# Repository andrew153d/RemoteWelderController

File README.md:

# RemoteWelderController #

A pair of devices meant to retrofit older welders with wireless connectivity. This document covers the usage and mechanical makeup, the cost overview can be found [here](https://github.com/andrew153d/RemoteWelderController/tree/main/hardware). There is also a preview of the site at this [link](https://andrew153d.github.io/RemoteWelderController/firmware/webpage/web_controller.html), note functionality is limited.

--- 

## Usage

There are three main modes of operation: Standard, Web Control, and Extended Web Control

### Standard Control

To enter standard control mode, toggle the Transmitter power switch to the 'ON' position and press the Power button on the Receiver. While the devices are searching for each other, their status LEDs will flash blue and will transition to solid green when connected. Rotation input on the control knob will result in proportional motion on the output shaft of the receiver. 

### Web Control

Web Control Mode will allow the user to make use of the web interface to control the output of the receiver. Press the power button on the receiver to turn the device on. After the status LED flashes blue, hold the power button for 3 seconds or until the LED turns to solid green. Connect your phone to the wifi network named Weld_---, open a browser and go to 'Weld.local'.

### Extended Web Control

Extended Web Control uses the Transmitter to host the webpage and repeats control to the receiver. After turning on both devices, hold both the up and down buttons for 3 seconds until the status LED turns green. Connect your phone to the Wifi network named Weld_--- and open the site 'Weld.Local'. In order to increase the usable distance, place the transmitter between the user and the receiver.

## Mechanical Details

### Web Interface 
<div align="center">
<p>
The webpage for control and configuration. Of course you can stay loyal to your brand while still bringing your welder into the modern world. The dial can be dragged to rotate, or the user can swipe the arrows at the bottom to rotate the knob. The lock button will match rotation on the output to the knob on the webpage. The align button will automatically measure the range of the output and scale the input accordingly. Settings and more configuration options can be accessed via the menu on the top left. 
</p>

</div>

### Transmitter

<div align="center">
<p>
Top view of the pelican case with reciever stowed on the right side.
</p>

</div>

<div align="center">

<p style="margin:0px 100px;">
The charge port cap can be removed to expose the USBC port and charge the device.
</p>

</div>

<div align="center">
<p style="margin:0px 100px;">
The circuit board and battery pack get mounted under the faceplate. Not shown is a cover to shield the electronics from debris under the faceplate.
</p>

</div>

### Receiver

<div align="center">
    <p>
        Receiver is shown without belt mechanism. The hatch is biased closed by a torsion spring and sealed against the surface with a O-ring.
    </p>

</div>
<div align="center">
    <p>
    Shown below is the hatch on the receiver that exposes the charging port, status led, and power button. The power button serves multiple alternative functions described in the usage section.
    </p>
    
</div>
<div align="center">
    <p>
    There are several seals on the receiver that maintain water resistance. The upper seal gets compressed between the upper cover and the case. There is also a seal on the access hatch as well as around the motor shaft.
    </p>

</div>

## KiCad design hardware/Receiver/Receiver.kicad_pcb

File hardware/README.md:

# BOM Overview and Cost #
This table is based on building 5 receivers and 5 transmitters. The total cost to build comes to $1050 and the individual cost to build of $210. Assuming four are sold at $300, the venture would profit $150.
## Transmitter ##

### Hardware Components ###

| Item                | QT per device | Total QT | Cost per device | Total Cost | Purchase QT | Purchase Cost |
|---------------------|---------------|----------|-----------------|------------|-------------|---------------|
| [Pelican Case](https://www.pelican.com/us/en/product/cases/protector/1120?sku=1120-000-110) | 1 | 5 | $45.00 | $225 | 5 | $225 |
| [Momentary Switches](https://a.co/d/eoz4Ket) | 2 | 10 | $1.5 | $15.00 | 12 | $18.00 |
| [Power Switch](https://a.co/d/50zdfZq) | 1 | 5 | $0.89 | $4.5 | 10 | $9.00 |
| Aluminum Face Plate | 1| 5 | $14.33 | $40.00 | 5 | $40.00 |
| [Knob](https://www.mcmaster.com/6094K42)| 1 | 5 | $5.28 | $26.40 | 5 | $28.00 |

## Receiver ##

### Hardware Components ###

| Item                | QT per device | Total QT | Cost per unit | Total Cost | Purchase QT | Purchase Cost |
|-|-|-|-|-|-|-|
| [Stepper](https://www.omc-stepperonline.com/e-series-nema-17-bipolar-1-8deg-17ncm-24-07oz-in-1a-42x42x23mm-4-wires-17he08-1004s)  | 1 | 5 | $4.26 | $21.30 | 5 | $25.00 |
| [Magnet Mounting Screws](https://www.mcmaster.com/catalog/130/3471/91772A107) | 4 | 20 | - | - | 100 | $6.50 |
| [Side Plate Mounting Screws](https://www.mcmaster.com/catalog/130/3432/91306A311) | 8 | 40 | - | - | 50 | 11.58 |
| [Magnets](https://a.co/d/8Z8Zce8)  | 2 | 10 | $2.12 | $22.00 | 12 | $26.00 |
| [Screws for feet](https://www.mcmaster.com/catalog/130/3471/91253A110) | 4 | 20 | - | - | 100 | 12.27 |
| [Upper O-Ring](https://www.mcmaster.com/1302N07/)| 1 | 5 | - | - | 25 | $12.03 |
| [Hatch O-Ring](https://www.mcmaster.com/1302N07/)| 1 | 5 | - | - | 25 | $12.03 |
| [Torsion Spring](https://www.mcmaster.com/9271K599)| 1 | 5 | - | - | 6 | $5.76 |
| Alumnium Legs | 1 | 5 | $2.38 | $20.38 | 10 | $23.00 |

## Common ##
| Item                | QT per pair | Total QT | Cost per unit | Total Cost | Purchase QT | Purchase Cost |
|---------------------|---------------|----------|---------------|------------|-------------|---------------|
| [18650 Batteries](https://www.18650batterystore.com/products/samsung-25r-18650) | 8 | 40 | $3.75 | $150 | 40 | $170 |
| [JST connector Pack](https://a.co/d/7OMg5ZO) | - | - | - | - | 1 | $26.00 |
| [Spot Welder](https://a.co/d/g4Re4Je) | - | - | - | - | 1 | $68.00 | 
| Misc wire | - | - | - | - | 1 | $20.00 |
| [Conformal Coating](https://a.co/d/c47sdoQ) | - | - | - | - | - | $35.44
| [Heat Shrink](https://a.co/d/8j2zc0W) | - | - | - | - | - | $10.00

### PCB Components ###
| Item/PN                | QT per device | Total QT | Cost per unit | Total Cost | Purchase QT | Purchase Cost |
|------------------------|---------------|----------|---------------|------------|-------------|---------------|
| All Components | alot | alot | 50 | 250 | alot | 250 |

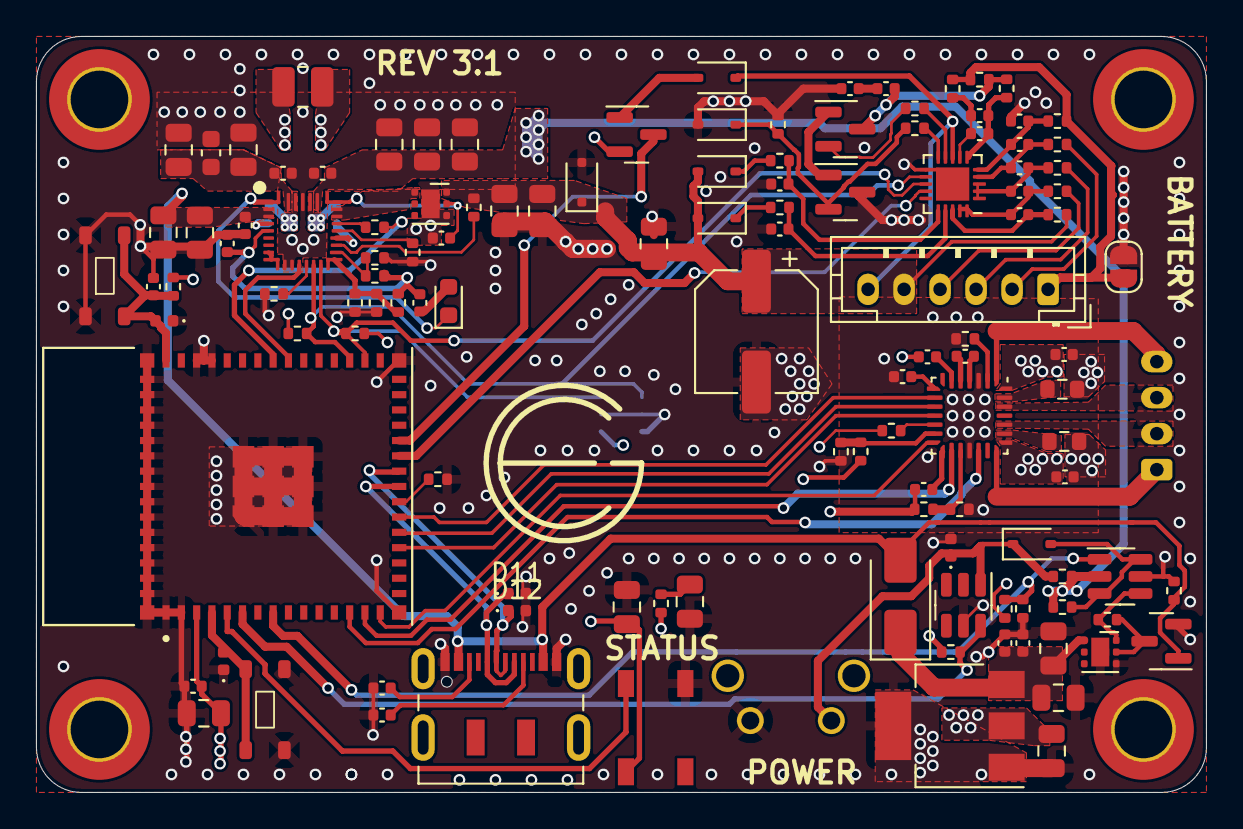
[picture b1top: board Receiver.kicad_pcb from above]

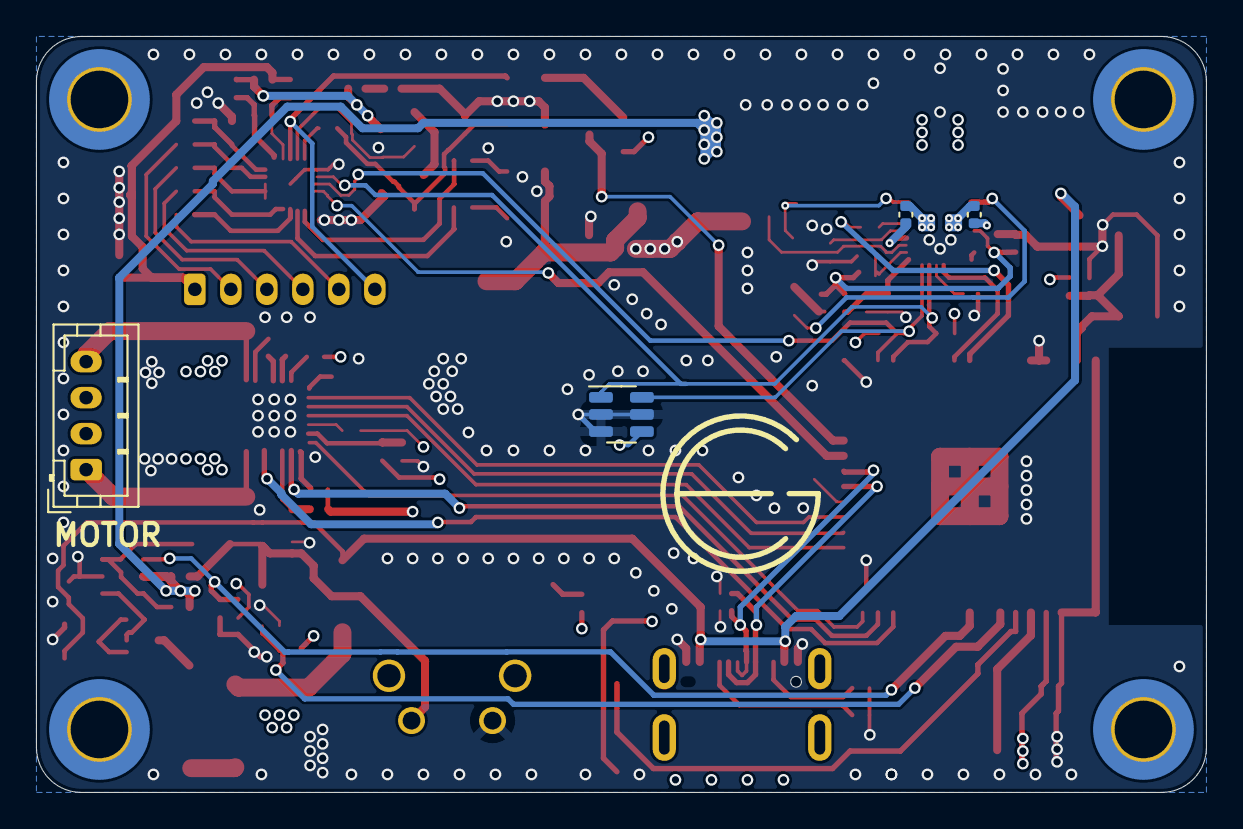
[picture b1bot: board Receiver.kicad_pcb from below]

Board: 4 copper layers, 65.0 x 42.0 mm, 131 parts (4 on the bottom side), 89 nets.

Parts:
A1: QFN-28_4x4mm_P0.5mm
BQ25792RQMR1: BQ25792
C1, C11, C29, C31, C35, C36, C39, C40, C44, C45, C47: 0.1u; C_0402_1005Metric
C2, C3, C6, C10, C12, C13, C15, C16, C17, C18, C26, C33, C34: 10u; C_0805_2012Metric
C4, C5: 47n; C_0402_1005Metric
C7: .1u; C_0402_1005Metric
C8: 10u; C_0603_1608Metric
C9: 4.7u; C_0402_1005Metric
C14: NP; C_0402_1005Metric
C21, C22, C23, C24, C25: 220nf; C_0402_1005Metric
C27, C30, C32, C38: 1u; C_0402_1005Metric
C28: 100p; C_0402_1005Metric
C37, C46: 22u; C_0805_2012Metric
C41: 47u; CP_Elec_6.3x5.4
C42, C43: 0.22u; C_0402_1005Metric
D1: LED; LED_0603_1608Metric
D2: LED; C_0805_2012Metric
D3: WS2812B; LED_WS2812B_PLCC4_5.0x5.0mm_P3.2mm
D4, D7, D8, D9, D10: 1N4148WQ-13-F; D_SOD-323
D5: D_Zener; D_SOD-323F
D6: EVVO SS16; D_SMA
D11, D12, D13, D14, D15: TVN3V3B1S; D_0402_1005Metric
H1, H2, H3, H4: MountingHole; MountingHole_3.2mm_M3_DIN965_Pad_TopBottom
J1: USB_C_Receptacle_USB2.0; USB_C_Receptacle_JAE_DX07S016JA1R1500
J3: JST_PH; JST_PH_B6B-PH-K_1x06_P2.00mm_Vertical
J4: Conn_01x04; JST_PH_B4B-PH-K_1x04_P2.00mm_Vertical
JP1: BQ76905_Bypass; SolderJumper-2_P1.3mm_Open_RoundedPad1.0x1.5mm
L1: 1u; L_1008_2520Metric
Q1: 2N7002; SOT-23
Q2, Q3: NMOS; SOT-23
Q4: PMOS; SOT-23
R1, R2, R16, R34, R35, R36, R38, R41, R45: 10k; R_0402_1005Metric
R3, R4, R5: 5.1k; C_0402_1005Metric
R6, R31, R32: 5.1k; R_0402_1005Metric
R7, R9, R11, R17, R18, R19, R20, R33, R39, R42: 100k; R_0402_1005Metric
R8: 1M; R_0402_1005Metric
R10, R26, R28, R29: 100; R_0402_1005Metric
R12: 127k; R_0402_1005Metric
R13: 5.24k; R_0402_1005Metric
R14: 30.31k; R_0402_1005Metric
R15: 6.04k; R_0402_1005Metric
R21, R22, R23, R24, R25: 10; R_0402_1005Metric
R27: 1m; R_0402_1005Metric
R30: 0; R_0402_1005Metric
R37: NP; R_0402_1005Metric
R40: 20k; R_0402_1005Metric
R43, R44: 68m; R_0603_1608Metric
SW1: Reset; Tactile_5.5mmx2.85mm
SW2: Boot; Tactile_5.5mmx2.85mm
SW3: 1825027-8; SW2_1825027-C_TEC
U1, U5: TPS22810DRV; WSON-6-1EP_2x2mm_P0.65mm_EP1x1.6mm
U2, U3: DMG6602SVTQ; TSOT-23-6
U4: TLV493DA1B6HTSA2; SOT-23-6
U6: BQ76905; UQFN-20-1EP_3x3mm_P0.4mm_EP1.85x1.85mm
U7: AZ1117-3.3; SOT-223
U8: ESP32-S3-MINI-1-N8; XCVR_ESP32-S3-MINI-1-N8

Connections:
+3.3V: C6.1, C37.1, C42.1, C44.1, C46.1, D3.1 (VDD), Q4.2 (G), R6.1, R7.1, R11.1, R34.1, R35.1, R36.1, R37.1, R40.1, R42.1, U4.4 (VDD), U7.2 (VO), U8.3 (3V3)
/ADDRS_LED: D3.4 (DIN), U8.5 (IO1)
/ALERT: U6.14 (ALERT), U8.25 (IO21)
/BAT+: A1.22 (VBB1), A1.28 (VBB2), C16.1, C18.1, C34.1, C39.1, C40.1, C41.1, C45.1, D5.1 (K), D7.2 (A), D8.2 (A), J3.5, R10.2, R21.1, U1.6 (VIN)
/BATP: BQ25792RQMR1.18 (BATP), R10.1
/BAT_C0: J3.1, JP1.1 (A), R25.1, R26.2, R27.1
/BAT_C1: J3.2, R24.1
/BAT_C2: J3.3, R23.1
/BAT_C3: J3.4, R22.1
/BC_INT: R2.2, U8.38 (IO42/TMS)
/BTST1: BQ25792RQMR1.4 (BTST1), C4.1
/BTST2: BQ25792RQMR1.19 (BTST2), C5.2
/CE: BQ25792RQMR1.13 (CE), R1.1
/CNTRL: D4.2 (A), R17.1, U2.3 (G2), U2.6 (D1)
/D+: D12.1 (A1), J1.A6 (D+), J1.B6 (D+), U8.24 (IO20/D+)
/D-: D11.1 (A1), J1.A7 (D-), J1.B7 (D-), U8.23 (IO19/D-)
/DIR: A1.19 (DIR), U8.13 (IO9)
/ESP_EN: C38.1, D14.2 (A2), R36.2, SW1.2, U8.45 (EN)
/ESP_IO0: D15.2 (A2), SW2.2, U8.4 (IO0_BOOT0)
/ILIM_HIZ: BQ25792RQMR1.17 (ILIM_HIZ), R12.1, R18.1
/INT: BQ25792RQMR1.21 (INT), R2.1
/MOT_nSLEEP: A1.14 (nSLEEP), U8.15 (IO11)
/MS1: A1.9 (MS1), U8.21 (IO17/DAC1)
/MS2: A1.10 (MS2), U8.20 (IO16)
/MS3: A1.11 (MS3), U8.19 (IO15)
/OUT1A: A1.24 (OUT1A), J4.2
/OUT1B: A1.21 (OUT1B), J4.1
/OUT2A: A1.26 (OUT2A), J4.3
/OUT2B: A1.1 (OUT2B), J4.4
/PMID: BQ25792RQMR1.29 (PMID), C7.1, C8.1, C10.1, C12.1
/PROG: BQ25792RQMR1.20 (PROG), R15.1
/QON: BQ25792RQMR1.12 (nQON), U8.37 (IO41/TDI)
/REGN: BQ25792RQMR1.5 (REGN), C9.1, R3.1, R12.2, R13.1
/ROSC: A1.13 (ROSC), R37.2, R38.1
/SCL: BQ25792RQMR1.14 (SCL), R35.2, U4.1 (SCL/INT), U6.12 (SCL), U8.33 (IO37)
/SDA: BQ25792RQMR1.15 (SDA), R34.2, U4.6 (SDA/ADDR), U6.13 (SDA), U8.32 (IO36)
/SDRV: BQ25792RQMR1.24 (SDRV), C14.1, U1.5 (EN/UVLO)
/SHUTDOWN: R7.2, R8.1, U2.1 (G1), U8.8 (IO4)
/STAT: BQ25792RQMR1.1 (STAT), D1.1 (K)
/STEP: A1.16 (STEP), U8.14 (IO10)
/SW: R11.2, U3.6 (D1), U8.6 (IO2)
/SW1: BQ25792RQMR1.28 (SW1), C4.2, L1.2
/SW2: BQ25792RQMR1.26 (SW2), C5.1, L1.1
/TS: D9.1 (K), J3.6, U6.8 (TS)
/VAC: BQ25792RQMR1.8 (VAC2), BQ25792RQMR1.9 (VAC1)
/VBAT: BQ25792RQMR1.22 (BAT), BQ25792RQMR1.23 (BAT), U1.1 (VOUT)
/VC0: C24.2, C25.1, R25.2, U6.5 (VC0)
/VC1: C23.2, C24.1, R24.2, U6.4 (VC1)
/VC2: C22.2, C23.1, R23.2, U6.1 (VC3A), U6.2 (VC3B), U6.3 (VC2)
/VC3: C21.2, C22.1, R22.2, U6.19 (VC4A), U6.20 (VC4B)
/VC4: C21.1, R21.2, U6.18 (VC5)
/VCP: A1.6 (VCP), C45.2
/VIN: C26.1, C27.1, C31.1, C33.1, D6.1 (K), U5.1 (VOUT), U7.3 (VI)
/VREF: A1.17 (REF), R40.2, R41.1
/VSYS: BQ25792RQMR1.25 (SYS), C11.1, C13.1, C15.1, C17.1, R9.1, R17.2, U2.2 (S2)
/VUSB: BQ25792RQMR1.2 (VBUS), BQ25792RQMR1.3 (VBUS), C1.1, C2.1, C3.1, D6.2 (A), J1.A4 (VBUS), J1.A9 (VBUS), J1.B4 (VBUS), J1.B9 (VBUS), Q1.1 (G), R19.1
/WAKE: Q4.3 (S), U8.26 (IO26)
GND: A1.3 (GND), A1.18 (GND), BQ25792RQMR1.10 (ACDRV2), BQ25792RQMR1.11 (ACDRV1), BQ25792RQMR1.27 (GND), C1.2, C2.2, C3.2, C6.2, C7.2, C8.2, C9.2, C10.2, C11.2, C12.2, C13.2, C14.2, C15.2, C16.2, C17.2, C18.2, C25.2, C26.2, C27.2, C30.2, C31.2, C32.2, C33.2, C34.2, C36.2, C37.2, C38.2, C39.2, C40.2, C41.2, C43.1, C44.2, C46.2, D2.1 (K), D3.3 (VSS), D5.2 (A), D10.2 (A), D11.2 (A2), D12.2 (A2), D13.2 (A2), D14.1 (A1), D15.1 (A1), J1.A1 (GND), J1.A12 (GND), J1.B1 (GND), J1.B12 (GND), JP1.2 (B), Q1.2 (S), Q3.3 (S), R1.2, R4.2, R5.2, R8.2, R14.2, R15.2, R16.2, R18.2, R19.2, R33.1, R38.2, R39.2, R41.2, R43.2, R44.2, R45.1, SW1.1, SW2.1, SW3.1, U1.4 (GND), U1.7 (GND), U2.5 (S1), U3.5 (S1), U4.2 (GND), U4.3 (GND), U4.5 (GND), U5.4 (GND), U5.7 (GND), U6.11 (VSS), U6.21 (VSS), U7.1 (GND), U7.4 (GND), U8.1 (GND), U8.2 (GND), U8.42 (GND), U8.43 (GND), U8.46 (GND), U8.47 (GND), U8.48 (GND), U8.49 (GND), U8.50 (GND), U8.51 (GND), U8.52 (GND), U8.53 (GND), U8.54 (GND), U8.55 (GND), U8.56 (GND), U8.57 (GND), U8.58 (GND), U8.59 (GND), U8.60 (GND), U8.61 (EXP), U8.62 (GND), U8.63 (GND), U8.64 (GND), U8.65 (GND)
unnamed: A1.4 (CP1), C47.1
unnamed: A1.5 (CP2), C47.2
unnamed: A1.23 (SENSE1), R43.1
unnamed: A1.27 (SENSE2), R44.1
unnamed: A1.15 (VDD), C42.2
unnamed: A1.8 (VREG), C43.2
unnamed: A1.2 (nEN), R39.1
unnamed: A1.12 (nRESET), R42.2
unnamed: BQ25792RQMR1.16 (TS), R13.2, R14.1, R16.1
unnamed: C35.2, C36.1
unnamed: D1.2 (A), R3.2
unnamed: D2.2 (A), R6.2
unnamed: D7.1 (K), R28.1
unnamed: D8.1 (K), R30.1
unnamed: D9.2 (A), Q4.1 (D)
unnamed: D10.1 (K), Q3.2 (G), R32.2, R33.2
unnamed: D4.1 (K), D13.1 (A1), R9.2, SW3.2, U3.1 (G1)
unnamed: J1.A5 (CC1), R4.1
unnamed: J1.B5 (CC2), R5.1
unnamed: Q1.3 (D), R20.1, U5.5 (EN/UVLO)
unnamed: Q2.1 (D), Q3.1 (D)
unnamed: Q2.2 (G), R31.2
unnamed: C35.1, Q2.3 (S), R27.2, R29.2
unnamed: R20.2, U2.4 (D2), U5.6 (VIN)
unnamed: C30.1, R28.2, U6.17 (BAT)
unnamed: R32.1, U6.10 (CHG)
unnamed: R31.1, U6.9 (DSG)
unnamed: C32.1, R30.2, U6.16 (REGSRC)
unnamed: C28.1, C29.1, R26.1, U6.7 (SRN)
unnamed: C28.2, C29.2, R29.1, U6.6 (SRP)
unnamed: R45.2, U8.22 (IO18/DAC2)

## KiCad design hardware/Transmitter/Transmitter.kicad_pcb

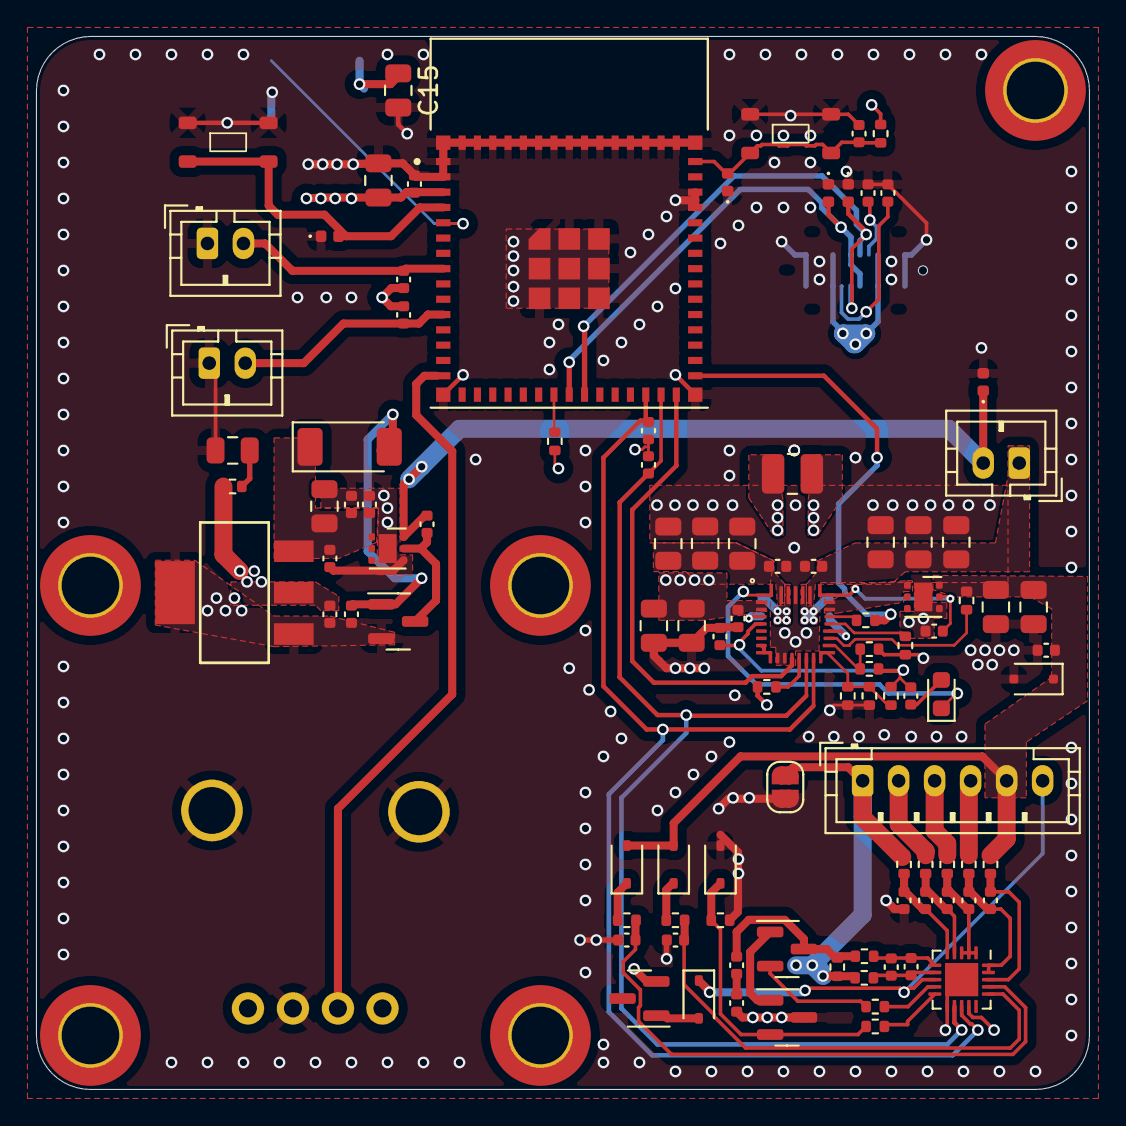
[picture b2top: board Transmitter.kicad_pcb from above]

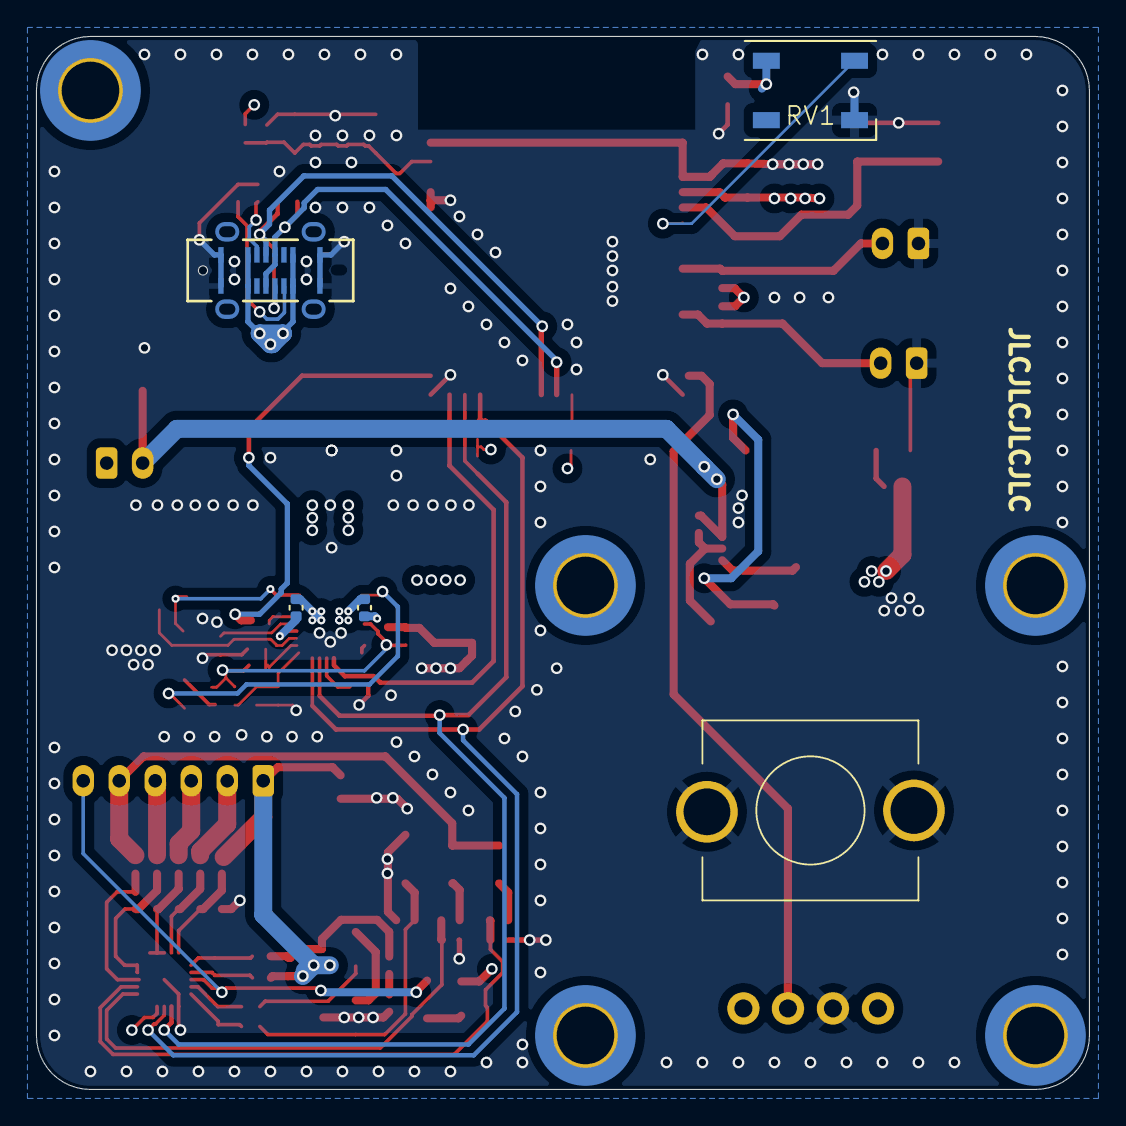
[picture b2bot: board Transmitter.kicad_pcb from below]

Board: 4 copper layers, 58.5 x 58.5 mm, 111 parts (5 on the bottom side), 65 nets.

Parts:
BQ25792RQMR1: BQ25792
C1, C10, C23, C28, C36, C39, C40: 0.1u; C_0402_1005Metric
C2, C5, C7, C9, C11, C12, C13, C14, C15, C16, C17, C18: 10u; C_0805_2012Metric
C3, C4: 47n; C_0402_1005Metric
C6: .1u; C_0402_1005Metric
C8: 4.7u; C_0402_1005Metric
C20, C29, C37, C38: 1u; C_0402_1005Metric
C21: 1n; C_0402_1005Metric
C24: 10uf; C_0402_1005Metric
C25: 10u; C_0402_1005Metric
C26: 22u; C_0402_1005Metric
C27: 22u; C_0805_2012Metric
C30, C31, C32, C33, C34: 220nf; C_0402_1005Metric
C35: 100p; C_0402_1005Metric
D1: LED; LED_0603_1608Metric
D2: LED; C_0805_2012Metric
D3: EVVOSS16; D_SOD-128
D4: D_Zener; D_SOD-323F
D5: WS2812B; LED_WS2812B_PLCC4_5.0x5.0mm_P3.2mm
D6, D7, D8, D9: 1N4148WQ-13-F; D_SOD-323
D10, D11, D12, D13, D14: TVN3V3B1S; D_0402_1005Metric
H1, H2, H3, H4, H5: MountingHole; MountingHole_3.2mm_M3_DIN965_Pad_TopBottom
J1: USB_C_Receptacle_USB2.0; CONN_GSB1CA11101DSHR_AMP
J2: UP_BTN; JST_PH_B2B-PH-K_1x02_P2.00mm_Vertical
J3: DN_BTN; JST_PH_B2B-PH-K_1x02_P2.00mm_Vertical
J6: JST_PH; JST_PH_B6B-PH-K_1x06_P2.00mm_Vertical
JP1: BQ76905_Bypass; SolderJumper-2_P1.3mm_Open_RoundedPad1.0x1.5mm
L1: 1u; L_1008_2520Metric
Q1: 2N7002; SOT-23
Q12, Q13: NMOS; SOT-23
Q14: PMOS; SOT-23
R1, R2, R16, R20, R22: 10k; R_0402_1005Metric
R3, R4, R5: 5.1k; C_0402_1005Metric
R6, R47, R48: 5.1k; R_0402_1005Metric
R7, R8, R9, R10: 100k; C_0402_1005Metric
R11, R42, R44, R45: 100; R_0402_1005Metric
R12: 127k; R_0402_1005Metric
R13: 5.24k; R_0402_1005Metric
R14: 30.31k; R_0402_1005Metric
R15: 6.04k; R_0402_1005Metric
R17, R49: 100k; R_0402_1005Metric
R18, R19: 10k; C_0402_1005Metric
R37, R38, R39, R40, R41: 10; R_0402_1005Metric
R43: 1m; R_0402_1005Metric
R46: 0; R_0402_1005Metric
RV1: R_Potentiometer; Potentiometer_Bourns_PVT111-3
SW1: Reset; Tactile_5.5mmx2.85mm
SW2: SW_SPST; JST_PH_B2B-PH-K_1x02_P2.00mm_Vertical
SW3: Boot; Tactile_5.5mmx2.85mm
U1, U2: TPS22810DRV; WSON-6-1EP_2x2mm_P0.65mm_EP1x1.6mm
U3: AZ1117-3.3; SOT223
U4: ESP32-S3-MINI-1-N8; XCVR_ESP32-S3-MINI-1-N8
U5: UQFN-20-1EP_3x3mm_P0.4mm_EP1.85x1.85mm

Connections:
+3.3V: C15.1, C26.1, C27.1, C28.1, D5.1 (VDD), Q14.2 (G), R6.1, R7.2, R10.2, R18.1, R19.1, R20.1, R22.1, RV1.1, U3.2 (VO), U4.3 (3V3)
/ADDRS_LED: D5.4 (DIN), U4.5 (IO1)
/BAT+: C14.1, C18.1, C24.1, D4.1 (K), D6.2 (A), D7.2 (A), J6.5, R11.2, R37.1, U2.6 (VIN)
/BATP: BQ25792RQMR1.18 (BATP), R11.1
/BAT_C0: J6.1, JP1.1 (A), R41.1, R42.2, R43.1
/BAT_C1: J6.2, R40.1
/BAT_C2: J6.3, R39.1
/BAT_C3: J6.4, R38.1
/BC_INT: R2.1, U4.31 (IO35)
/BTST1: BQ25792RQMR1.4 (BTST1), C3.1
/BTST2: BQ25792RQMR1.19 (BTST2), C4.2
/CE: BQ25792RQMR1.13 (CE), R1.2
/D+: D12.2 (A2), J1.A6 (D+), J1.B6 (D+), U4.24 (IO20/D+)
/D-: D13.2 (A2), J1.A7 (D-), J1.B7 (D-), U4.23 (IO19/D-)
/DN_BTN: J3.2, R10.1, U4.11 (IO7)
/ESP_EN: C29.1, D11.2 (A2), R20.2, SW1.2, U4.45 (EN)
/ESP_IO0: D10.2 (A2), SW3.2, U4.4 (IO0_BOOT0)
/ILIM_HIZ: BQ25792RQMR1.17 (ILIM_HIZ), R12.1, R17.1
/INT: BQ25792RQMR1.21 (INT), R2.2
/PMID: BQ25792RQMR1.29 (PMID), C6.1, C7.1, C9.1, C11.1
/POT: RV1.2, U4.15 (IO11)
/PROG: BQ25792RQMR1.20 (PROG), R15.1
/QON: BQ25792RQMR1.12 (nQON), U4.30 (IO48)
/REGN: BQ25792RQMR1.5 (REGN), C8.1, R3.1, R12.2, R13.1
/SCL: BQ25792RQMR1.14 (SCL), R19.2, U4.29 (IO34), U5.12 (SCL)
/SDA: BQ25792RQMR1.15 (SDA), R18.2, U4.28 (IO33), U5.13 (SDA)
/SDRV: BQ25792RQMR1.24 (SDRV), C21.1, U2.5 (EN/UVLO)
/STAT: BQ25792RQMR1.1 (STAT), D1.1 (K)
/SW1: BQ25792RQMR1.28 (SW1), C3.2, L1.2
/SW2: BQ25792RQMR1.26 (SW2), C4.1, L1.1
/TS: D8.1 (K), J6.6, U5.8 (TS)
/UP_BTN: J2.2, R7.1, U4.8 (IO4)
/VAC: BQ25792RQMR1.8 (VAC2), BQ25792RQMR1.9 (VAC1)
/VBAT: BQ25792RQMR1.22 (BAT), BQ25792RQMR1.23 (BAT), U2.1 (VOUT)
/VBUS: C16.1, C20.1, C23.1, C25.1, D3.1 (K), U1.1 (VOUT), U3.3 (VI)
/VC0: C33.2, C34.1, R41.2, U5.5 (VC0)
/VC1: C32.2, C33.1, R40.2, U5.4 (VC1)
/VC2: C31.2, C32.1, R39.2, U5.1 (VC3A), U5.2 (VC3B), U5.3 (VC2)
/VC3: C30.2, C31.1, R38.2, U5.19 (VC4A), U5.20 (VC4B)
/VC4: C30.1, R37.2, U5.18 (VC5)
/VSYS: BQ25792RQMR1.25 (SYS), C10.1, C12.1, C13.1, C17.1, SW2.1 (A)
/VUSB: BQ25792RQMR1.2 (VBUS), BQ25792RQMR1.3 (VBUS), C1.1, C2.1, C5.1, D3.2 (A), J1.A4 (VBUS), J1.A9 (VBUS), J1.B4 (VBUS), J1.B9 (VBUS), Q1.1 (G), R8.1
GND: BQ25792RQMR1.10 (ACDRV2), BQ25792RQMR1.11 (ACDRV1), BQ25792RQMR1.27 (GND), C1.2, C2.2, C5.2, C6.2, C7.2, C8.2, C9.2, C10.2, C11.2, C12.2, C13.2, C14.2, C15.2, C16.2, C17.2, C18.2, C20.2, C21.2, C23.2, C24.2, C25.2, C26.2, C27.2, C28.2, C29.2, C34.2, C37.2, C38.2, C40.2, D2.1 (K), D4.2 (A), D5.3 (VSS), D9.2 (A), D10.1 (A1), D11.1 (A1), D12.1 (A1), D13.1 (A1), D14.2 (A2), J1.A1 (GND), J1.A12 (GND), J1.B1 (GND), J1.B12 (GND), J2.1, J3.1, JP1.2 (B), Q1.2 (S), Q13.3 (S), R1.1, R4.2, R5.2, R8.2, R14.2, R15.2, R16.2, R17.2, R49.1, RV1.3, SW1.1, SW3.1, U1.4 (GND), U1.7 (GND), U2.4 (GND), U2.7 (GND), U3.1 (GND), U3.4 (GND), U4.1 (GND), U4.2 (GND), U4.42 (GND), U4.43 (GND), U4.46 (GND), U4.47 (GND), U4.48 (GND), U4.49 (GND), U4.50 (GND), U4.51 (GND), U4.52 (GND), U4.53 (GND), U4.54 (GND), U4.55 (GND), U4.56 (GND), U4.57 (GND), U4.58 (GND), U4.59 (GND), U4.60 (GND), U4.61 (EXP), U4.62 (GND), U4.63 (GND), U4.64 (GND), U4.65 (GND), U5.11 (VSS), U5.21 (VSS)
unnamed: BQ25792RQMR1.16 (TS), R13.2, R14.1, R16.1
unnamed: C39.2, C40.1
unnamed: D1.2 (A), R3.2
unnamed: D2.2 (A), R6.2
unnamed: D6.1 (K), R44.1
unnamed: D7.1 (K), R46.1
unnamed: D8.2 (A), Q14.1 (D)
unnamed: D9.1 (K), Q13.2 (G), R48.2, R49.2
unnamed: D14.1 (A1), R9.2, SW2.2 (B), U1.6 (VIN)
unnamed: J1.A5 (CC1), R4.1
unnamed: J1.B5 (CC2), R5.1
unnamed: Q1.3 (D), R9.1, U1.5 (EN/UVLO)
unnamed: Q12.1 (D), Q13.1 (D)
unnamed: Q12.2 (G), R47.2
unnamed: C39.1, Q12.3 (S), R43.2, R45.2
unnamed: R22.2, U4.22 (IO18/DAC2)
unnamed: C37.1, R44.2, U5.17 (BAT)
unnamed: R48.1, U5.10 (CHG)
unnamed: R47.1, U5.9 (DSG)
unnamed: C38.1, R46.2, U5.16 (REGSRC)
unnamed: C35.1, C36.1, R42.1, U5.7 (SRN)
unnamed: C35.2, C36.2, R45.1, U5.6 (SRP)

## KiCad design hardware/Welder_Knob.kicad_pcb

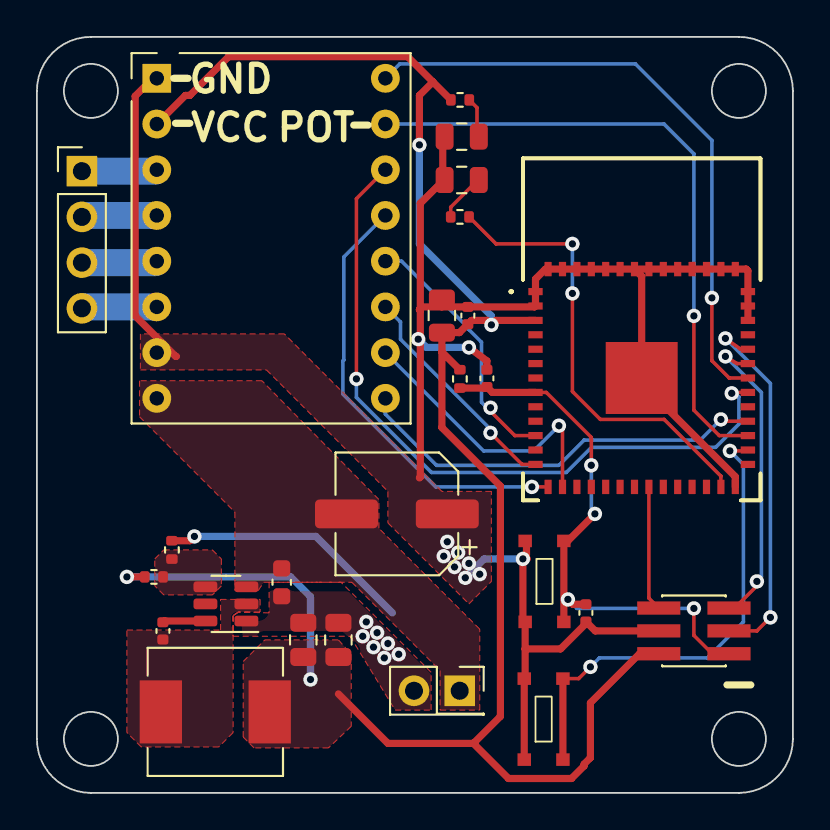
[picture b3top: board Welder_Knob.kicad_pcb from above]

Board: 2 copper layers, 42.0 x 42.0 mm, 25 parts (0 on the bottom side), 26 nets.

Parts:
A7: Pololu_Breakout_A4988; Pololu_Breakout-16_15.2x20.3mm
C7: 10u; C_0603_1608Metric
C8, C12, C14: 0.1u; C_0402_1005Metric
C9, C10, C11: 22u; C_0805_2012Metric
C13: 1u; C_0402_1005Metric
C16: 47u; CP_Elec_6.3x5.9
D7, D8: LED; C_0805_2012Metric
IC7: ESP32-C3-MINI-1-N4; ESP32MINI1N4
J7: Power; PinSocket_2x01_P2.54mm_Vertical
J8: UART; PinHeader_2x03_P1.27mm_Vertical_SMD
J9: Motor_Header; PinHeader_1x04_P2.54mm_Vertical
L7: 3.3u; L_Sunlord_MWSA0618S
R7: 31.6k; R_0402_1005Metric
R8, R10: 10k; R_0402_1005Metric
R9, R11: 5.1k; R_0402_1005Metric
SW7: Reset; button_RKB2SJK250SMTR LFS
SW8: General Input; button_RKB2SJK250SMTR LFS
U7: TSOT-23-6

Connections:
+3.3V: A7.2 (VDD), C9.1, C10.1, C11.1, C12.1, IC7.3 (3V3), J8.2, L7.2, R7.1, R9.1, R10.1
+12V: A7.8 (VMOT), C7.1, C16.2, J7.1, U7.3 (VIN)
/BST: C8.1, U7.6 (BST)
/FB: R7.2, R8.1, U7.4 (FB)
/SW: C8.2, L7.1, U7.2 (SW)
Button: IC7.29 (IO5), SW8.2
ESP_EN: C13.1, C14.1, IC7.8 (EN), J8.1, R10.2, SW7.2
ESP_IO0: IC7.21 (IO0), J8.6
ESP_RXD: IC7.35 (RXD0), J8.5
ESP_TXD: IC7.36 (TXD0), J8.3
GND: A7.1 (GND), A7.7 (GND), C7.2, C9.2, C10.2, C11.2, C12.2, C13.2, C14.2, C16.1, D7.1 (K), D8.1 (K), IC7.1 (GND_1), IC7.2 (GND_2), IC7.27 (GND), IC7.38 (GND), IC7.39 (GND), IC7.40 (GND), IC7.41 (GND), IC7.42 (GND), IC7.43 (GND), IC7.44 (GND), IC7.45 (GND), IC7.46 (GND), IC7.47 (GND), IC7.48 (GND), IC7.49 (GND), IC7.50 (GND), IC7.51 (GND), IC7.52 (GND), IC7.53 (GND), IC7.54 (GND), IC7.55 (GND), J7.2, J8.4, R8.2, SW7.1, SW8.1, U7.1 (GND)
MOT_DIR: A7.16 (DIR), IC7.34 (IO21)
MOT_EN: A7.9 (~ENABLE), IC7.31 (IO23)
MOT_RST: A7.13 (~RESET), IC7.14 (IO26)
MOT_SLEEP: A7.14 (~SLEEP), IC7.33 (IO22)
MOT_STEP: A7.15 (STEP), IC7.30 (IO18)
MS1: A7.10 (MS1), IC7.15 (IO27)
MS2: A7.11 (MS2), IC7.13 (IO25)
MS3: A7.12 (MS3), IC7.11 (IO32)
M_1A: A7.4 (1A), J9.2
M_1B: A7.3 (1B), J9.1
M_2A: A7.5 (2A), J9.3
M_2B: A7.6 (2B), J9.4
unnamed: D7.2 (A), R9.2
unnamed: D8.2 (A), R11.2
S_LED: IC7.26 (IO10), R11.1

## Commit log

2023-10-22 add render
2024-03-10 Release 1.0
2024-03-10 Add image
2024-03-12 Completed Power Path
2024-03-13 Completed Transmitter Schematic
2024-03-16 Transmitter PCB complete
2024-03-17 Finished Receiver Schematic
2024-03-17 Completed Receiver PCB
2024-03-18 add ibom to git ignore
2024-03-18 Removed old files
2024-03-19 Revision 1.2 of receiver board
2024-03-19 Begin bom
2024-03-19 Add bms to schematic
2024-03-21 BMS added to hardware
2024-03-22 update costs and finalize dxf for laser cutting
2024-03-23 updates to bom cost
2024-03-25 working upload on esp32s3
2024-03-25 working custom board
2024-03-25 Webiste building script
2024-03-25 Add mDNS
2024-03-26 rename battery leads, update footprints
2024-03-27 update mcu to ESP32S3
2024-03-27 Add board definition
2024-03-28 update UI
2024-03-29 change CDC mode to allow Serial printing
2024-03-30 Add udp debug statements
2024-03-30 add torsion spring
2024-04-01 Add 3d models
2024-04-03 Add cell balancing
2024-04-04 remove backups from git
2024-04-04 remove backups
2024-04-04 add battery balancing IC
2024-04-05 add battery balancing to transmitter
2024-04-05 remove transmitter backups
2024-04-06 finalize cost estimate
2024-04-06 add images
2024-04-06 update readme details
2024-04-06 fix image warping
2024-04-06 add extended range
2024-04-06 add bom link
2024-04-08 update website
2024-04-08 add slider functionality
2024-04-08 add menu
2024-04-08 add manufacturer colors
2024-04-09 apply background color
2024-04-09 revert function compression
2024-04-09 update to dewalt
2024-04-11 update build script to include css and js
2024-04-11 update expanding menu
2024-04-12 update battery display
2024-04-12 add battery levels
2024-04-13 add tvs diodes
2024-04-16 add stitching vias
2024-04-16 modify webpage generation process
2024-04-16 remove dead code
2024-04-17 update emc
2024-04-26 create bom
2024-05-27 PCB revision
